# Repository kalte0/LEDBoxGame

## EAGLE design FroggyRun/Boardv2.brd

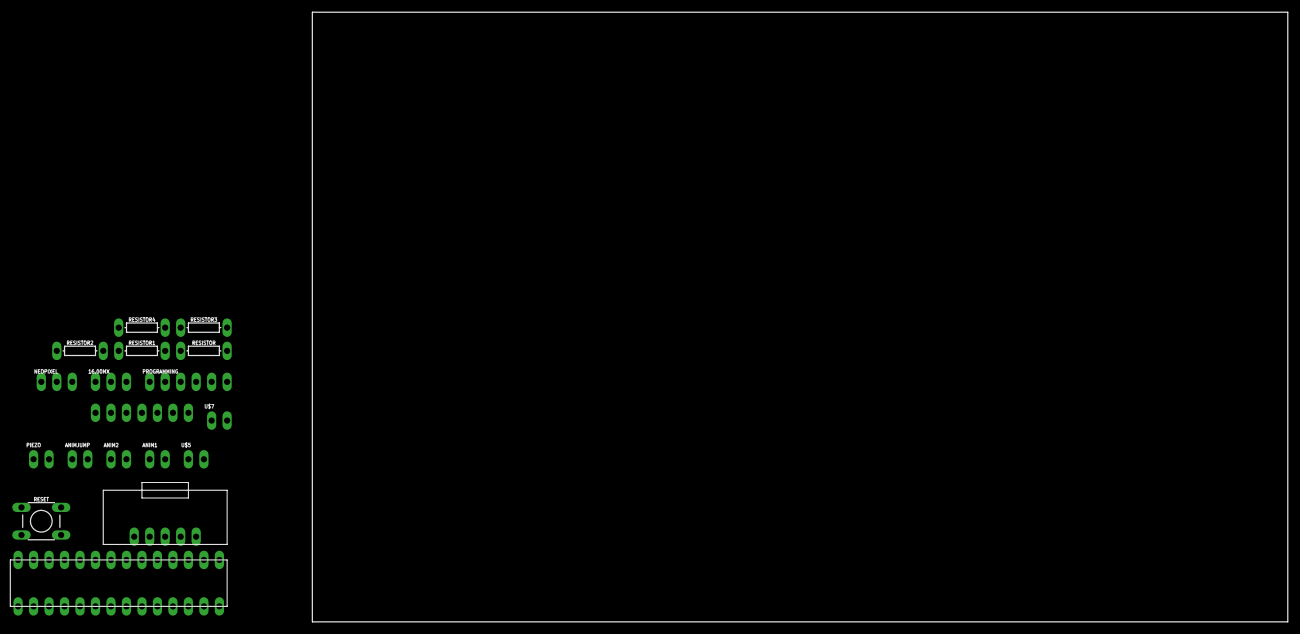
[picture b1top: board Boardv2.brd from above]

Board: 2 copper layers, 160.0 x 100.0 mm, 18 parts (0 on the bottom side), 21 nets, no tracks yet.

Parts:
16.00MX: RESONATOR; 1X03_NO_SILK
ANIM1, ANIM2: LED; 1X02_LONGPADS
ANIMJUMP: LED; 1X02_LONGPADS
NEOPIXEL: 1X3; 1X03_NO_SILK
PIEZO: 1X2; 1X02_LONGPADS
PROGRAMMING: 1X6; 1X06_NO_SILK
RESET: MOMENTARY_SWITCH; TACTILE_SWITCH_PTH_6.0MM
RESISTOR, RESISTOR1: 10k; AXIAL-0.3
RESISTOR2, RESISTOR3, RESISTOR4: 470; AXIAL-0.3
U$1: ATMEGA328
U$2: USB
U$5: BUTTON(OFFBOARD); 1X02_LONGPADS
U$6: OLED
U$7: CAPACITOR; 1X02_LONGPADS

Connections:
5V: NEOPIXEL.1, PROGRAMMING.4, RESISTOR.P$2, U$1.7, U$1.20, U$2.5V, U$5.2, U$6.VIN, U$7.1
ANIM1: ANIM1.1, U$1.4
ANIM2: ANIM2.1, U$1.5
ANIMJUMP: ANIMJUMP.1, U$1.6
GND: 16.00MX.2, NEOPIXEL.3, PIEZO.2, PROGRAMMING.6, RESET.1, RESET.3, RESISTOR1.P$2, RESISTOR2.P$2, RESISTOR3.P$2, RESISTOR4.P$2, U$1.8, U$1.21, U$2.GND, U$6.GND, U$7.2
unnamed: ANIM1.2, RESISTOR2.P$1
unnamed: ANIM2.2, RESISTOR3.P$1
unnamed: PROGRAMMING.3, U$1.2
unnamed: ANIMJUMP.2, RESISTOR4.P$1
unnamed: RESISTOR1.P$1, U$1.11, U$5.1
unnamed: 16.00MX.1, U$1.9
unnamed: 16.00MX.3, U$1.10
unnamed: U$1.15, U$6.DATA
unnamed: U$1.16, U$6.CLK
unnamed: U$1.17, U$6.SA0
unnamed: U$1.18, U$6.CS
unnamed: U$1.19, U$6.RST
NEOPIXEL: NEOPIXEL.2, U$1.12
PIEZO: PIEZO.1, U$1.13
PROGRAMMING: PROGRAMMING.2, U$1.3
RESET: RESET.2, RESET.4, RESISTOR.P$1, U$1.1

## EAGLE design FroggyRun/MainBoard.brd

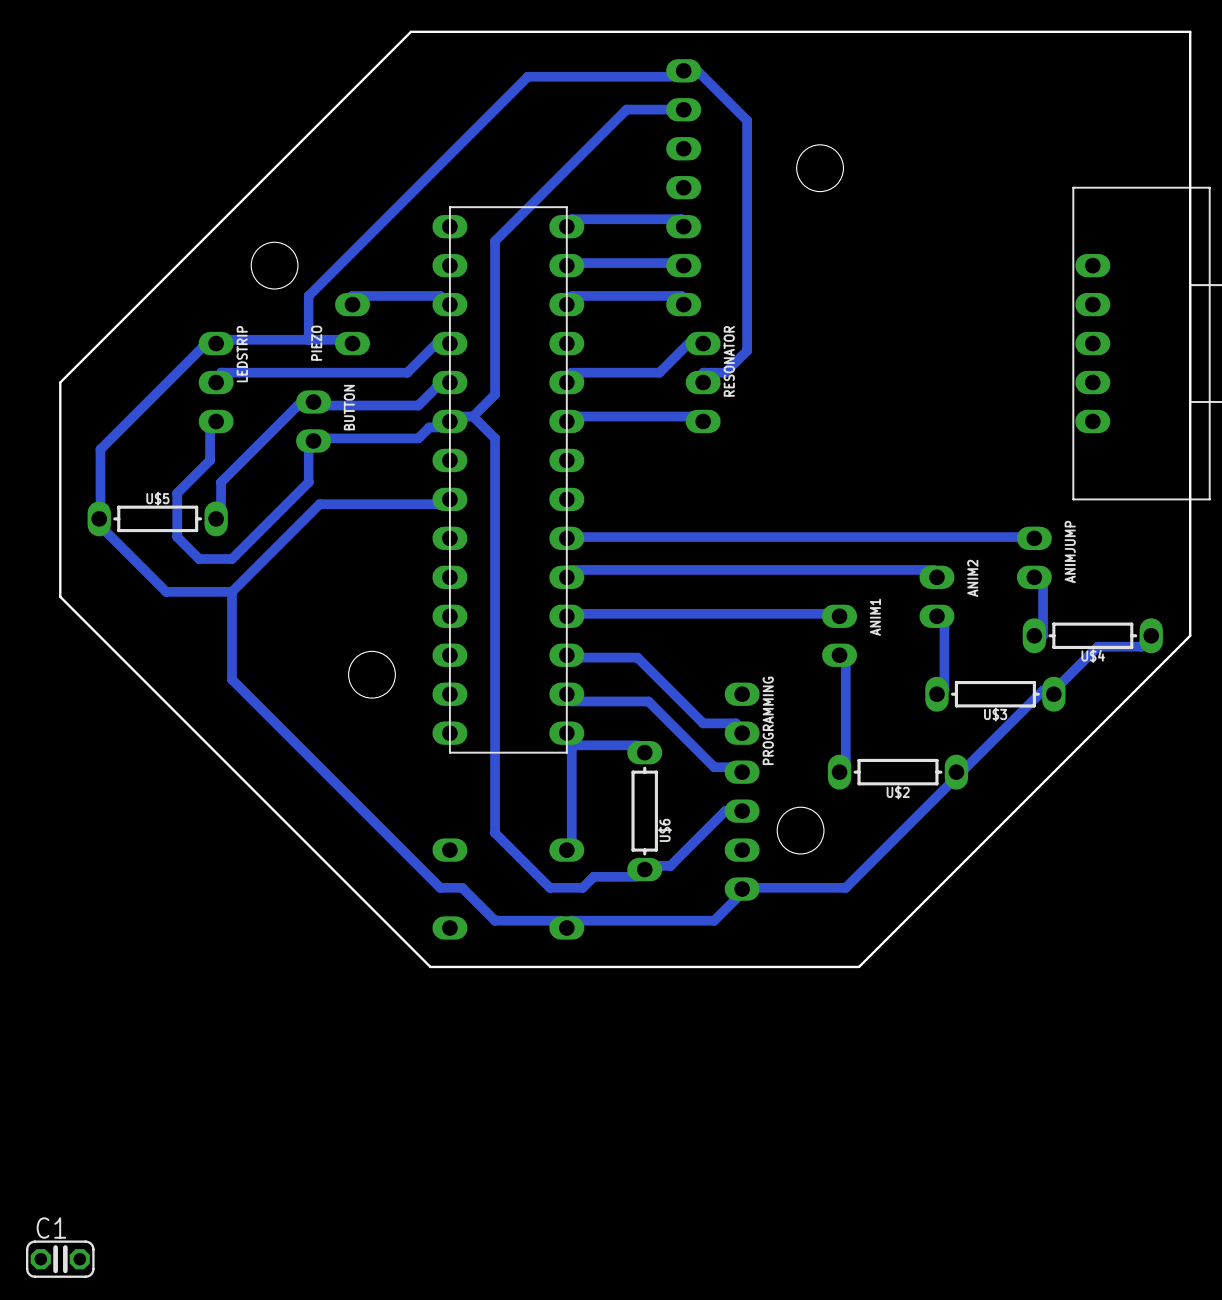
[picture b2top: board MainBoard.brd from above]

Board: 2 copper layers, 73.7 x 61.0 mm, 18 parts (0 on the bottom side), 21 nets.

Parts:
ANIM1, ANIM2: 1X2; 1X02_LONGPADS
ANIMJUMP: 1X2; 1X02_LONGPADS
BUTTON: 1X2; 1X02_LONGPADS
C1: C025-024X044
LEDSTRIP: 1X3; 1X03_NO_SILK
OLED: OLED
PIEZO: 1X2; 1X02_LONGPADS
PROGRAMMING: 1X6; 1X06_NO_SILK
RESONATOR: 1X3; 1X03_NO_SILK
U$1: ATMEGA328
U$2, U$3, U$4, U$5, U$6: 1k; AXIAL-0.3
U$7: BUTTON
USBPOWER: USB

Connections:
GND: C1.2, LEDSTRIP.1, OLED.GND, PIEZO.1, PROGRAMMING.6, RESONATOR.2, U$1.8, U$1.22, U$2.P$1, U$3.P$1, U$4.P$1, U$5.P$1, U$7.P$1, USBPOWER.GND
unnamed: BUTTON.1, U$1.19, U$5.P$2
unnamed: LEDSTRIP.2, U$1.18
unnamed: OLED.DATA, U$1.12
unnamed: OLED.CLK, U$1.13
unnamed: OLED.SA0, U$1.14
unnamed: OLED.CS, U$1.15
unnamed: OLED.RST, U$1.16
unnamed: PIEZO.2, U$1.17
unnamed: ANIM1.2, U$2.P$2
unnamed: ANIM2.2, U$3.P$2
unnamed: ANIMJUMP.2, U$4.P$2
unnamed: ANIM1.1, U$1.4
unnamed: ANIM2.1, U$1.5
unnamed: ANIMJUMP.1, U$1.6
unnamed: RESONATOR.3, U$1.9
unnamed: RESONATOR.1, U$1.10
RESET: U$1.1, U$6.P$1, U$7.P$2
RX: PROGRAMMING.3, U$1.2
TX: PROGRAMMING.2, U$1.3
VIN: BUTTON.2, C1.1, LEDSTRIP.3, OLED.VIN, PROGRAMMING.4, U$1.7, U$1.20, U$6.P$2

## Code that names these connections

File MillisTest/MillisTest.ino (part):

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#define NICKNAME 4

// ----------------------PINS-----------------
#define ANIM1 2 // ANIM1 should be the run animation in the front. Will be the first to activate during run animation. 
#define ANIM2 3
#define ANIMJUMP 4
#define PIN 6 // For Neopixel strip. 
#define BUTTON 5
#define PIEZO 7

// -------------------OLED DISPLAY---------------
#define OLED_MOSI  9
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

void setup() {
  pinMode(ANIM1, OUTPUT);
  pinMode(ANIM2, OUTPUT);
  pinMode(ANIMJUMP, OUTPUT);
  pinMode(PIN, OUTPUT);
  pinMode(BUTTON, INPUT);
  Serial.begin(9600);
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
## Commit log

2019-02-13 LED RUn aniamtino wow
2019-02-15 Code upload
2019-08-28 ajksdfl
2019-08-29 The real code was the friends we made along the way
2019-08-29 Starting to work on tsuff
2019-09-03 push
2019-09-03 added bit defines
2019-09-03 added Macros
2019-09-05 IT'S ALIVE!
2019-09-09 rewq
2019-09-10 fdsa
2019-09-10 adsf
2019-09-18 DXFSSSSSSSSSSSSSSSSS
    lmao yea
2019-09-23 Button Holder
2019-09-23 added schematic + board from eagle
2019-09-23 Took Board for fusion
2019-09-26 added finshed eagle file with USB
2019-09-27 Dxfs added
2019-09-27 put new board in fusion
2019-10-08 ghkj
2019-10-09 dxf stuff
2019-10-15 gkl,fdfalkj;
2019-10-15 Added Final Board -- some errors with F/B annoation in Eagle
2019-10-18 Added board to 3d design
2019-10-21 add code for Nickname screen
2019-10-23 Nickname section completely implemented!!
2019-10-24 add EEPROM save-- almost working
2019-10-25 Added New DXFs
2019-10-25 fixed number save in EEPROM
2019-10-28 workin
2020-03-11 Last Changes to the box. change y to z, and change display style
